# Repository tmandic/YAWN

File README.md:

# YAWN - Your Autonomous Wireless Node
This repository presents the developed hardware and software for wireless node based on PIC16LF1459. The repository includes schematic and gerber files. Furthermore, the software libraries are added for basic node functionality.

# Hardware description
uC: PIC16LF1459 low power microcontroller programmable through header U4 (pins 11-15)

communication modules: nRF24L01+ (SPI) or BLE HM-11 (UART)

sensors: HDC1080 (temperature and humidity sensor) and OPT3001 (light sensor)

power supply: 1.5 F supercapacitor or CR2032 battery. The supercapacictor can be charged through USB port, or through expansions header (i.e. energy harvesting module aka shield, connected to YAWN)

LED: two green and red signalling LED 

push buttons: 4 general purpose push buttons and RESET button

timer: for long interval and minmum sleep current consumption

jumpers: J1-J4 push buttons select jumpers, J5-J6 power supply configuration, J7-J8 DONE pin (timer is used) selector, J11 - VCAP monitor, all other jumpers are header pin selectors

(c) University of Zagreb Faculty of Electrical Engineering and Computing

_Authors : T. Mandic, N. Budimir, A. Baric

_Version : 5

_Date : 2018/05/05

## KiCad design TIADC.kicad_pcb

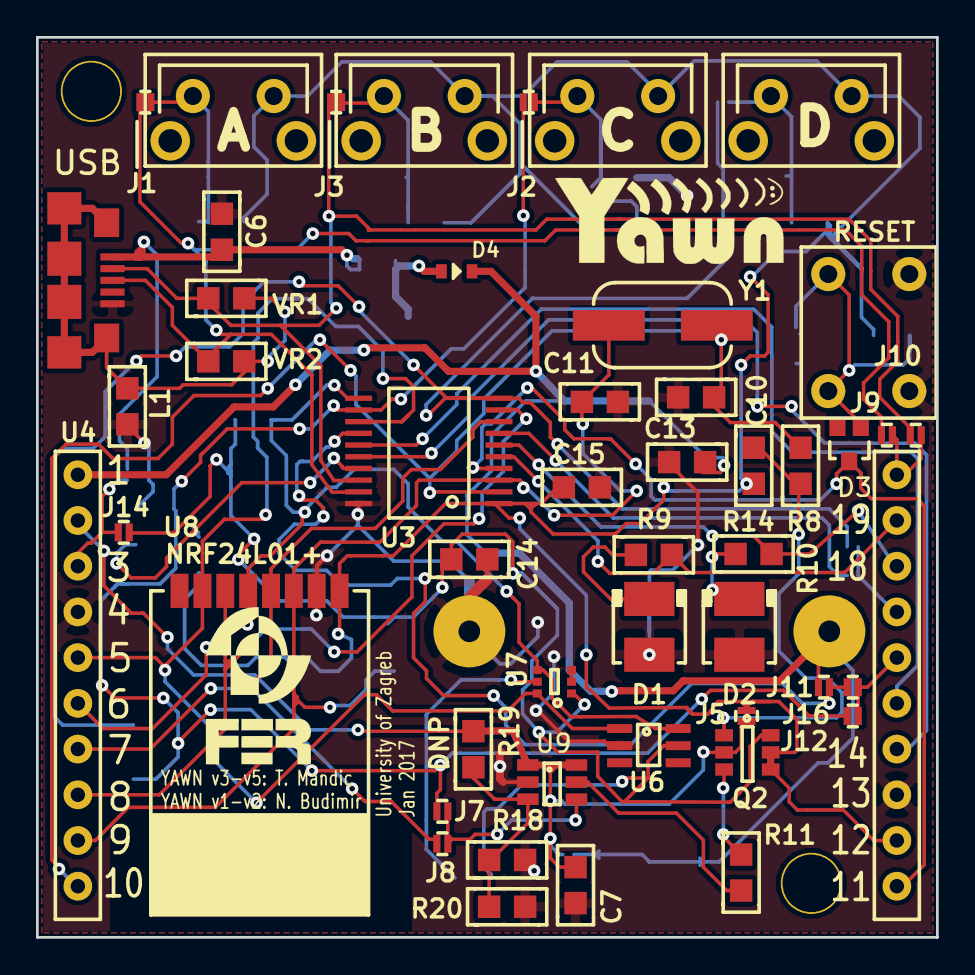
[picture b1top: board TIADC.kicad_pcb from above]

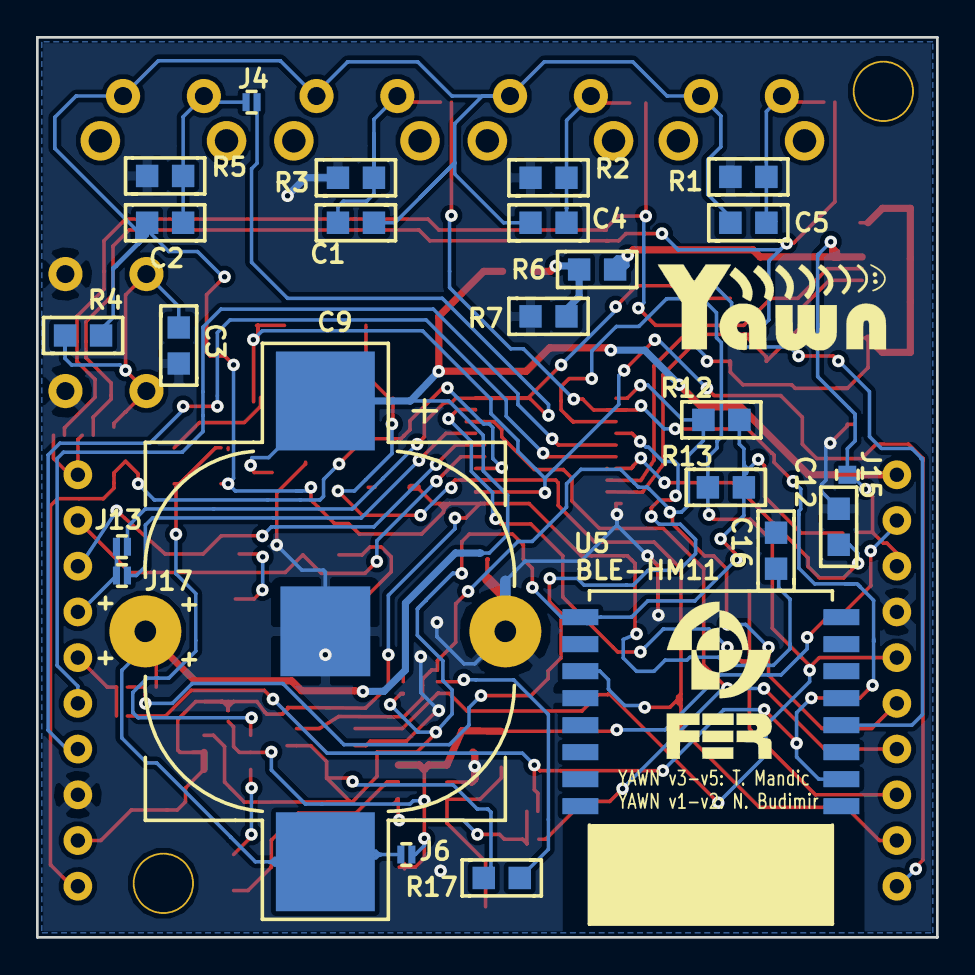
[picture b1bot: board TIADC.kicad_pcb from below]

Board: 2 copper layers, 50.0 x 50.0 mm, 72 parts (24 on the bottom side), 43 nets.

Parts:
C1, C2, C3, C4, C5, C7, C14, C15: 100nF; 0805
C6: 10uF; 0805
C9: 1.5F; CAP&BAT
C10, C11: 18pF; 0805
C12: 220nF; 0805
C13: 22uF; 0805
C16: 1uF; 0805
D1: redled; PLCC2
D2: greenled; PLCC2
D3: BAT54W; SOT-323D
D4: DA2S10100L; SOD-523
J1, J2, J3, J4, J5, J6, J7, J8, J9, J10, J11, J12, J13, J14, J15, J16, J17: JUMPER; J1x04
L1: BLM21; 0805
Q2: FDC6312P; SSOT-6
R1, R2, R3, R5, R14: 47k; 0805
R4: 220k; 0805
R6: 30; 0805
R7: 100; 0805
R8, R11: 220; 0805
R9, R10: 820R; 0805
R12, R13, R17: 10k; 0805
R18, R20: R; 0805
R19: DNP; 0805
SW1: RESET
SW2: A; SPST
SW3: B; SPST
SW4: C; SPST
SW5: D; SPST
U1: USB; USBMICRO
U3: PIC16(L)F1459; SSOP-20
U4: 2x10pin_header; HEADER
U5: BLE-HM11; HM-11
U6: HDC1080; PWSON-N6
U7: OPT3001; USON-6
U8: NRF24L01+; NRF24L01+-mini
U9: TPL5110; SOT-23-6
VR1, VR2: VR; 0805
Y1: 12 MHz; HC49-US

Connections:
/AN0: J11.2, J16.1, U3.14
/AN1: J17.1, U3.7
/CE: C11.1, U3.3, U4.9, U5.11, U8.3, Y1.2
/D+: J1.1, J9.1, U1.3, U3.19, VR2.1
/D-: J3.1, J10.1, U1.2, U3.18, VR1.1
/DONE: J7.2, J8.2, U9.4
/GPIO0: R10.1, U3.6, U4.18
/GPIO1: R9.1, U3.5, U4.19
/H3: J14.2, J15.2, U4.3
/H16: J12.2, J16.2, U4.16
/H17: J13.2, J17.2, U4.17
/H20: J9.2, J10.2, U4.20
/ICSPCLK: U3.15, U4.15
/ICSPDAT: U3.16, U4.14
/IRQ: C10.1, R8.1, U3.2, U4.10, Y1.1
/RX/DT: J2.1, J7.1, J12.1, U3.12, U5.2
/SCL/SCK: R12.2, U3.11, U4.6, U6.6, U7.4, U8.5
/SDA/SDI: R13.2, U3.13, U4.5, U6.1, U7.6, U8.7
/SDO: U3.9, U4.8, U8.6
/SWA: C5.2, J1.2, R1.2, SW2.2
/SWB: C4.2, J3.2, R2.2, SW3.2
/SWC: C1.2, J2.2, R3.2, SW4.2
/SWD: C2.2, J4.2, R5.2, SW5.2
/TX/CK: J4.1, J13.1, U3.10, U5.4
/VCAP: C9.1, C13.1, D4.1, J6.2, J11.1, U4.1
/VDD: C1.1, C2.1, C4.1, C5.1, C15.1, C16.1, J5.2, Q2.4, Q2.5, R4.2, R14.2, SW2.1, SW3.1, SW4.1, SW5.1, U3.1, U4.12, U8.1
/VDDX: C7.1, J5.1, J6.1, Q2.2, R19.1, U4.2, U9.1, U9.6
/VDDY: C14.1, J14.1, Q2.6, R12.1, R13.1, R17.2, U5.9, U6.5, U7.1
/VUSB: C6.1, J15.1, R6.1, U1.1
/\MCLR: D3.3, U3.4, U4.11
/\SS: J8.1, U3.8, U4.7, U8.4
GND: C3.2, C6.2, C7.2, C9.2, C10.2, C11.2, C12.2, C13.2, C14.2, C15.2, C16.2, D1.1, D2.1, L1.2, R1.1, R2.1, R3.1, R5.1, R7.2, R18.2, R20.2, SW1.2, U1.5, U3.20, U4.4, U4.13, U5.12, U6.2, U7.2, U7.3, U8.2, U9.2
unnamed: C3.1, D3.1, R4.1, SW1.1
unnamed: C12.1, U3.17
unnamed: D1.2, R9.2
unnamed: D2.2, R10.2
unnamed: D4.2, R6.2, R7.1
unnamed: L1.1, U1.6, VR1.2, VR2.2
unnamed: Q2.1, R8.2, R14.1
unnamed: Q2.3, R11.1
unnamed: R11.2, U9.5
unnamed: R17.1, U7.5
unnamed: R18.1, R19.2, R20.1, U9.3

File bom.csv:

Reference, Value, Footprint, Datasheet, Farnell, Q10+ (GBP), Comment
"C9","1.5F","komponente:CAP&BAT","","2472074+2115303","2.78+0.683",""
"U7","OPT3001","komponente:USON-6","","2466963","2.46",""
"L1","BLM21","komponente:0805","","1515661","0.0536",""
"U1","USB","komponente:USBMICRO","","2293755","0.522",""
"C12","220nF","komponente:0805","","2074517","0.0281",""
"R6","15","komponente:0805","","2447576","0.005",""
"C6","10uF","komponente:0805","","2320833","0.15",""
"SW4","C","komponente:SPST","","1555987","0.0766",""
"SW5","D","komponente:SPST","","1555987","0.0766",""
"SW2","A","komponente:SPST","","1555987","0.0766",""
"U5","BLE-HM11","komponente:HM-11","","ebay","7.3",""
"R10","820R","komponente:0805","","2074517","0.0281",""
"D1","redled","komponente:PLCC2","","1328348","0.238",""
"D2","greenled","komponente:PLCC2","","1659076","0.257",""
"SW3","B","komponente:SPST","","1555987","0.0766",""
"U6","HDC1080","komponente:PWSON-N6","","2535017","4.13",""
"R17","10k","komponente:0805","","9332391","0.0018",""
"Y1","12 MHz","komponente:HC49-US","","2467681","0.305",""
"C10","18pF","komponente:0805","","2497020","0.0293",""
"C11","18pF","komponente:0805","","2497020","0.0293",""
"R9","820R","komponente:0805","","2074517","0.0281",""
"R1","47k","komponente:0805","","1469929","0.0164",""
"R2","47k","komponente:0805","","1469929","0.0164",""
"R3","47k","komponente:0805","","1469929","0.0164",""
"R5","47k","komponente:0805","","1469929","0.0164",""
"SW1","RESET","komponente:RESET","","2456210","0.172",""
"R4","220k","komponente:0805","","9234292","0.013",""
"R14","47k","komponente:0805","","1469929","0.0164",""
"R12","10k","komponente:0805","","9332391","0.0018",""
"R13","10k","komponente:0805","","9332391","0.0018",""
"U9","TPL5110","komponente:SOT-23-6","","2471145","0.832",""
"VR2","VR","komponente:0805","","8832463","0.502",""
"VR1","VR","komponente:0805","","8832463","0.502",""
"U3","PIC16(L)F1459","komponente:SSOP-20","","2305825","1.20",""
"R18","R","komponente:0805",""
"Q2","FDC6312P","komponente:SSOT-6","","1700713","0.0958",""
"R19","DNP","komponente:0805",""
"R20","R","komponente:0805",""
"C13","1uF","komponente:0805","","2112709","0.41",""
"C15","100nF","komponente:0805","","1759167","0.0115",""
"C16","10uF","komponente:0805","","2320833","0.15",""
"J2","JUMPER","komponente:J1x04",""
"J1","JUMPER","komponente:J1x04",""
"J4","JUMPER","komponente:J1x04",""
"J3","JUMPER","komponente:J1x04",""
"J6","JUMPER","komponente:J1x04",""
"J5","JUMPER","komponente:J1x04",""
"J10","JUMPER","komponente:J1x04",""
"J9","JUMPER","komponente:J1x04",""
"J11","JUMPER","komponente:J1x04",""
"J8","JUMPER","komponente:J1x04",""
"J7","JUMPER","komponente:J1x04",""
"J13","JUMPER","komponente:J1x04",""
"J12","JUMPER","komponente:J1x04",""
"U4","2x10pin_header","komponente:HEADER","","1667516","2.04","2x (price doubled)"
"U8","NRF24L01+","komponente:NRF24L01+-mini","","ebay","0.9",""
"J15","JUMPER","komponente:J1x04",""
"J14","JUMPER","komponente:J1x04",""
"J16","JUMPER","komponente:J1x04",""
"J17","JUMPER","komponente:J1x04",""
"R7","360","komponente:0805","","2323839","0.013",""
"D4","DA3X101K0L","komponente:SOT-23","","2284128","0.0293",""
"R8","220","komponente:0805","","9332804","0.0018",""
"D3","BAT54W","komponente:SOT-323D","","1081197","0.17",""
"R11","220","komponente:0805","","9332804","0.0018",""
"C4","100nF","komponente:0805","","1759167","0.0115",""
"C1","100nF","komponente:0805","","1759167","0.0115",""
"C2","100nF","komponente:0805","","1759167","0.0115",""
"C5","100nF","komponente:0805","","1759167","0.0115",""
"C3","100nF","komponente:0805","","1759167","0.0115",""
"C7","100nF","komponente:0805","","1759167","0.0115",""
"C14","100nF","komponente:0805","","1759167","0.0115",""

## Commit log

2017-05-26 Added MIC to project files
